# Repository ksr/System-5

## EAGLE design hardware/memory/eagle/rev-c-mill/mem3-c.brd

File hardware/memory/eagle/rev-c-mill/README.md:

# Memory Rev C mill (2014)

The 2005 Rev C, re-routed in 2014 for milling the PCB.
It was saved from a newer Eagle, so the file is XML; `fab/` holds its CAM job.

Compared with the 2005 Rev C board (`../rev-c/fusion-export/mem3-c.brd`, compared 2026-10-05):

| | 2005 Rev C | 2014 mill |
|---|---|---|
| Parts, positions, values | 50 parts | identical |
| Connectivity | 92 nets | identical |
| Board outline | 140 × 96 mm | identical |
| Track segments (top / bottom) | 1007 / 623 | 868 / 503 |
| Vias | 165 | 132 |
| Track width | 10 mil | 10 mil |

The circuit is unchanged; only the routing differs, with fewer vias to drill and pin by hand.
Nothing in the tree shows whether it was actually milled.

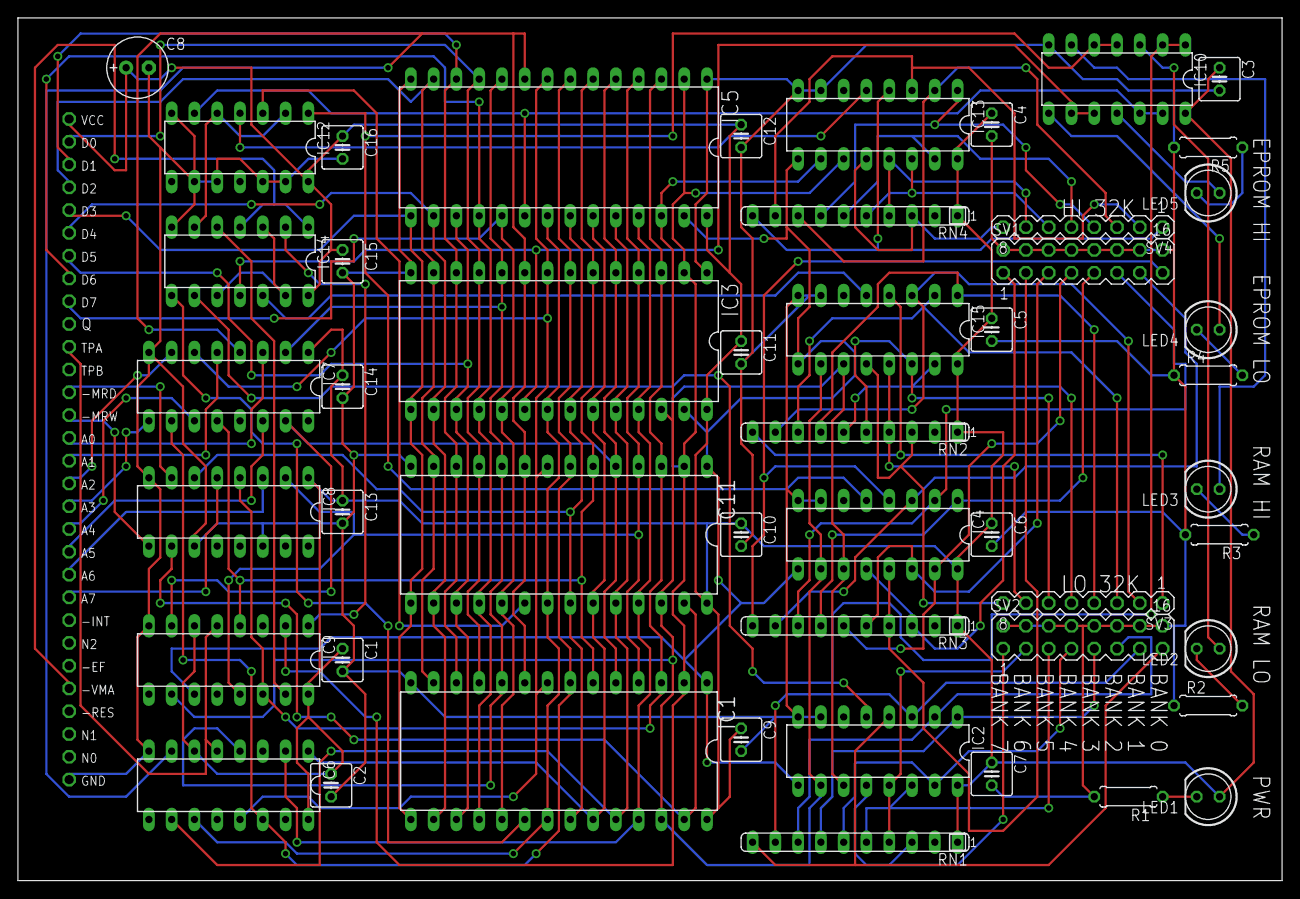
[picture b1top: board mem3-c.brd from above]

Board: 2 copper layers, 140.9 x 96.2 mm, 50 parts (0 on the bottom side), 92 nets.

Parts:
C1, C2, C3, C4, C5, C6, C7, C9, C10, C11, C12, C13, C14, C15, C16: .1; C025-050X050
C8: 10.0; E2,5-7
IC1, IC11: 62256; DIL28-6
IC2, IC4, IC13, IC15: 74LS151N; DIL16
IC3, IC5: 27256; DIL28
IC6, IC9: 4042N; DIL16
IC7, IC8: 4050N; DIL16
IC10: 74LS00N; DIL14
IC12, IC14: 74LS32N; DIL14
LED1, LED2, LED3, LED4, LED5: LED5MM
R1, R2, R3, R4, R5: 470; 0207/7
RN1, RN2, RN3, RN4: SIL10
SV1, SV2: MA08-2
SV3, SV4: MA08-1
U$1: C30

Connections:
BUFFADDR0: IC1.10, IC3.10, IC5.10, IC6.4, IC7.2, IC11.10
BUFFADDR1: IC1.9, IC3.9, IC5.9, IC6.7, IC7.4, IC11.9
BUFFADDR2: IC1.8, IC3.8, IC5.8, IC6.13, IC7.6, IC11.8
BUFFADDR3: IC1.7, IC3.7, IC5.7, IC6.14, IC7.10, IC11.7
BUFFADDR4: IC1.6, IC3.6, IC5.6, IC7.12, IC9.4, IC11.6
BUFFADDR5: IC1.5, IC3.5, IC5.5, IC7.15, IC9.7, IC11.5
BUFFADDR6: IC1.4, IC3.4, IC5.4, IC8.2, IC9.13, IC11.4
BUFFADDR7: IC1.3, IC3.3, IC5.3, IC8.4, IC9.14, IC11.3
BUFFADDR8: IC1.25, IC3.25, IC5.25, IC6.2, IC11.25
BUFFADDR9: IC1.24, IC3.24, IC5.24, IC6.10, IC11.24
BUFFADDR10: IC1.21, IC3.21, IC5.21, IC6.11, IC11.21
BUFFADDR11: IC1.23, IC3.23, IC5.23, IC6.1, IC11.23
BUFFADDR12: IC1.2, IC2.11, IC3.2, IC4.11, IC5.2, IC9.2, IC11.2, IC13.11, IC15.11
BUFFADDR13: IC1.26, IC2.10, IC3.26, IC4.10, IC5.26, IC9.10, IC11.26, IC13.10, IC15.10
BUFFADDR14: IC1.1, IC2.9, IC3.27, IC4.9, IC5.27, IC9.11, IC11.1, IC13.9, IC15.9
BUFFADDR15: IC9.1, IC14.2
BUSDATA0: IC1.11, IC3.11, IC5.11, IC11.11, U$1.2
BUSDATA1: IC1.12, IC3.12, IC5.12, IC11.12, U$1.3
BUSDATA2: IC1.13, IC3.13, IC5.13, IC11.13, U$1.4
BUSDATA3: IC1.15, IC3.15, IC5.15, IC11.15, U$1.5
BUSDATA4: IC1.16, IC3.16, IC5.16, IC11.16, U$1.6
BUSDATA5: IC1.17, IC3.17, IC5.17, IC11.17, U$1.7
BUSDATA6: IC1.18, IC3.18, IC5.18, IC11.18, U$1.8
BUSDATA7: IC1.19, IC3.19, IC5.19, IC11.19, U$1.9
GND: C1.2, C2.2, C3.2, C4.2, C5.2, C6.2, C7.2, C8.-, C9.2, C10.2, C11.2, C12.2, C13.2, C14.2, C15.2, C16.2, IC1.14, IC2.7, IC2.8, IC3.1, IC3.14, IC4.7, IC4.8, IC5.1, IC5.14, IC6.8, IC7.8, IC8.8, IC8.11, IC8.14, IC9.8, IC10.7, IC11.14, IC12.7, IC12.9, IC12.10, IC12.12, IC12.13, IC13.7, IC13.8, IC14.7, IC15.7, IC15.8, R1.2, R2.1, R3.2, R4.1, R5.2, SV1.2, SV1.4, SV1.6, SV1.8, SV1.10, SV1.12, SV1.14, SV1.16, SV2.2, SV2.4, SV2.6, SV2.8, SV2.10, SV2.12, SV2.14, SV2.16, U$1.30
unnamed: LED1.K, R1.1
unnamed: IC2.12, RN1.3, SV2.1
unnamed: IC2.13, RN1.4, SV2.3
unnamed: IC2.14, RN1.5, SV2.5
unnamed: IC6.5, IC9.5, U$1.11
unnamed: IC2.15, RN1.6, SV2.7
unnamed: IC7.3, U$1.15
unnamed: IC7.5, U$1.16
unnamed: IC7.7, U$1.17
unnamed: IC7.9, U$1.18
unnamed: IC7.11, U$1.19
unnamed: IC7.14, U$1.20
unnamed: IC8.3, U$1.21
unnamed: IC8.5, U$1.22
unnamed: IC2.1, RN1.7, SV2.9
unnamed: IC2.2, RN1.8, SV2.11
unnamed: IC2.3, RN1.9, SV2.13
unnamed: IC2.4, RN1.10, SV2.15
unnamed: IC10.8, LED4.A
unnamed: IC12.2, IC12.5, IC14.6
unnamed: IC4.12, RN3.3, SV1.1
unnamed: IC4.13, RN3.4, SV1.3
unnamed: IC4.14, RN3.5, SV1.5
unnamed: IC4.15, RN3.6, SV1.7
unnamed: IC8.9, U$1.14
unnamed: IC8.7, U$1.13
unnamed: IC14.1, IC14.4, U$1.26
unnamed: IC4.1, RN3.7, SV1.9
unnamed: IC4.2, RN3.8, SV1.11
unnamed: IC4.3, RN3.9, SV1.13
unnamed: IC14.3, IC14.10, IC14.13
unnamed: LED4.K, R4.2
unnamed: IC4.4, RN3.10, SV1.15
unnamed: IC2.5, IC10.1, IC10.2, IC14.9
unnamed: IC1.20, IC14.8
unnamed: IC14.12, IC15.5
unnamed: IC5.20, IC10.12, IC10.13, IC12.6
unnamed: IC13.13, RN4.4, SV4.7
unnamed: IC13.14, RN4.5, SV4.6
unnamed: IC13.15, RN4.6, SV4.5
unnamed: IC13.1, RN4.7, SV4.4
unnamed: IC13.2, RN4.8, SV4.3
unnamed: IC13.3, RN4.9, SV4.2
unnamed: IC3.20, IC10.9, IC10.10, IC14.11
unnamed: IC13.12, RN4.3, SV4.8
unnamed: IC13.4, RN4.10, SV4.1
unnamed: IC11.20, IC12.3
unnamed: IC12.4, IC13.5
unnamed: IC9.15, IC14.5
unnamed: IC4.5, IC10.4, IC10.5, IC12.1
unnamed: IC15.12, RN2.3, SV3.8
unnamed: LED5.K, R5.1
unnamed: IC10.11, LED5.A
unnamed: IC10.3, LED2.A
unnamed: LED2.K, R2.2
unnamed: IC15.13, RN2.4, SV3.7
unnamed: LED3.K, R3.1
unnamed: IC10.6, LED3.A
unnamed: IC15.14, RN2.5, SV3.6
unnamed: IC15.15, RN2.6, SV3.5
unnamed: IC15.1, RN2.7, SV3.4
unnamed: IC15.2, RN2.8, SV3.3
unnamed: IC15.3, RN2.9, SV3.2
unnamed: IC15.4, RN2.10, SV3.1
RD: IC1.22, IC3.22, IC5.22, IC8.6, IC11.22
VCC: C1.1, C2.1, C3.1, C4.1, C5.1, C6.1, C7.1, C8.+, C9.1, C10.1, C11.1, C12.1, C13.1, C14.1, C15.1, C16.1, IC1.28, IC2.16, IC3.28, IC4.16, IC5.28, IC6.6, IC6.16, IC7.1, IC8.1, IC9.6, IC9.16, IC10.14, IC11.28, IC12.14, IC13.16, IC14.14, IC15.16, LED1.A, RN1.1, RN2.1, RN3.1, RN4.1, U$1.1
WR: IC1.27, IC8.10, IC11.27
